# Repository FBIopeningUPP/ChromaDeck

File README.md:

# ChromaDeck

this project is basically a midi deivce that is good and i lov eit

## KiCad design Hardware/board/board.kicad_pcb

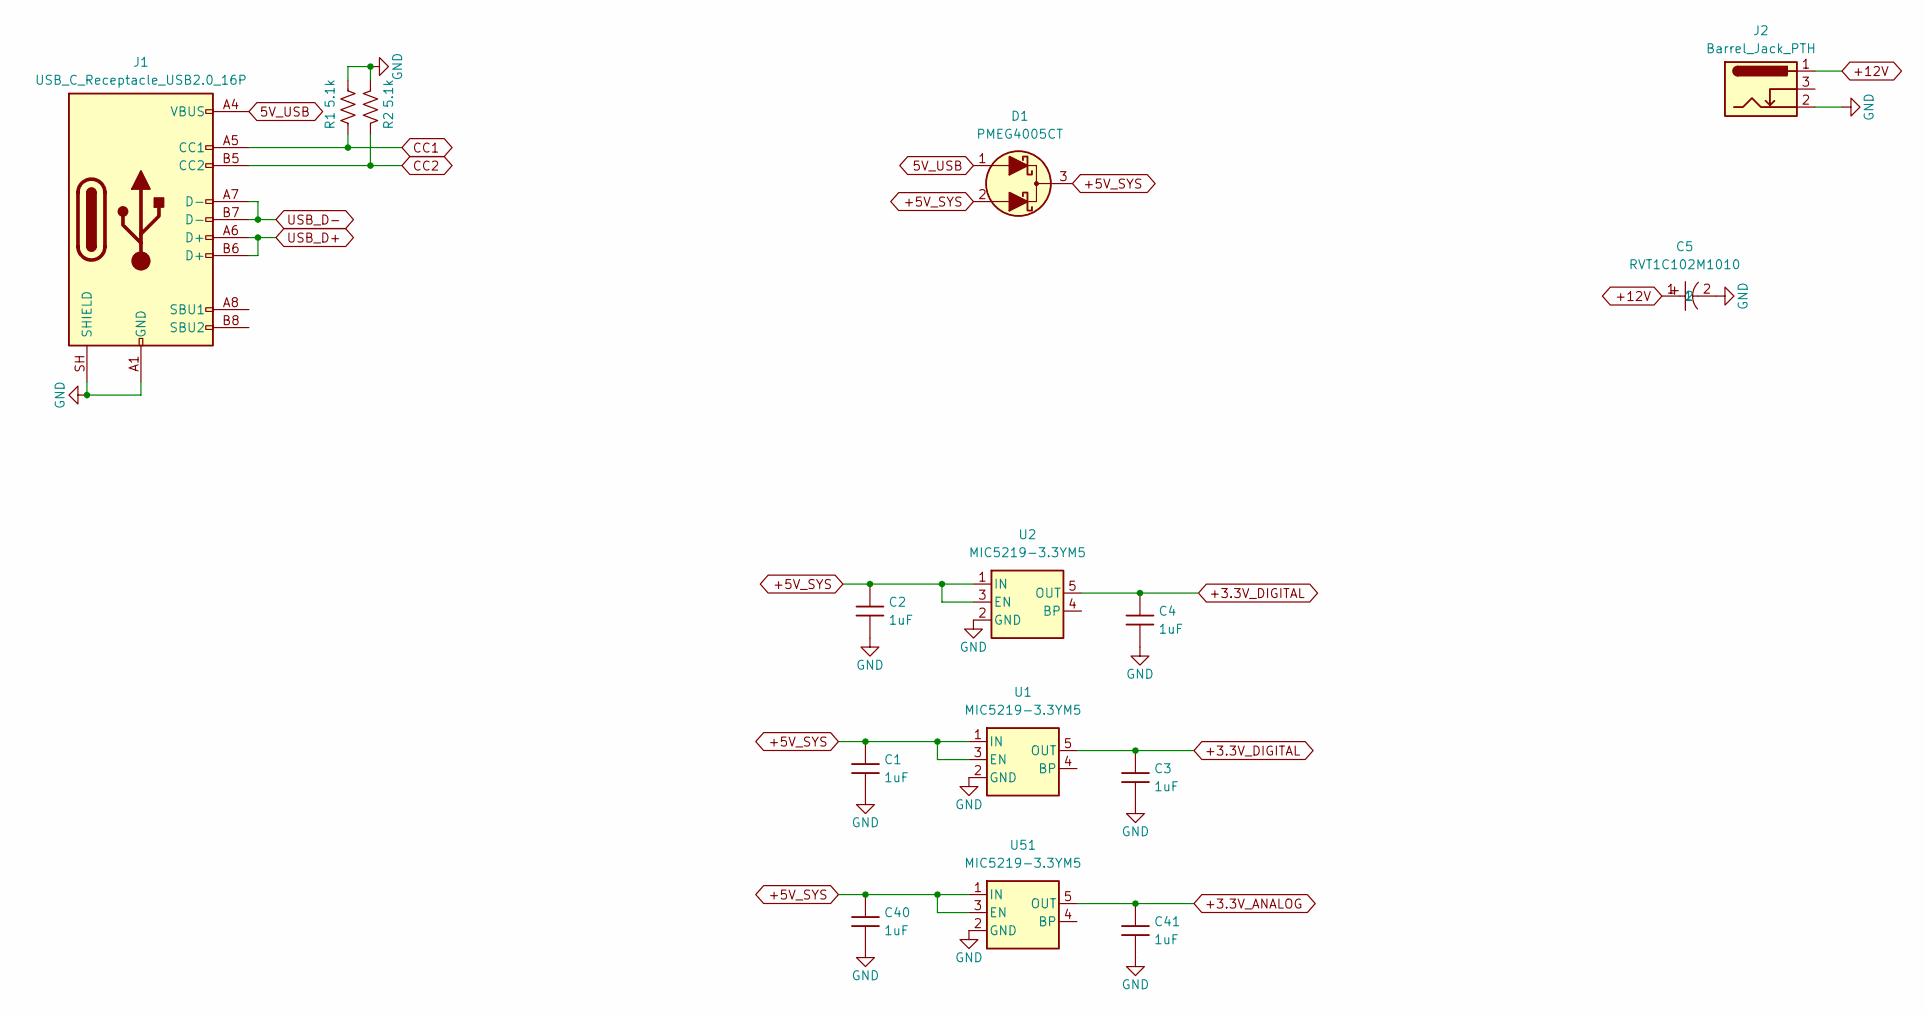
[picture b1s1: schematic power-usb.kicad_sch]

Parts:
C1, C2, C3, C4, C40, C41: 1uF; C_0603
C5: RVT1C102M1010; CAP-SMD_BD10.0-L10.3-W10.3-LS11.3-FD; MPN RVT1C102M1010; LCSC Part C72470
D1: PMEG4005CT; SOT-23
J1: USB_C_Receptacle_USB2.0_16P; USB_C_Receptacle_GCT_USB4105-xx-A_16P_TopMnt_Horizontal
J2: Barrel_Jack_PTH; BarrelJack_CUI_PJ-102AH_Horizontal
R1, R2: 5.1k; R_0603_1608Metric
U1, U2, U51: MIC5219-3.3YM5; SOT-23-5

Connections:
5V_USB: D1.1 (A2), J1.A4 (VBUS), J1.A9 (VBUS), J1.B4 (VBUS), J1.B9 (VBUS)
+3.3V_ANALOG: C41.1, U51.5 (OUT); also elsewhere on the board
+3.3V_DIGITAL: C3.1, C4.1, U1.5 (OUT), U2.5 (OUT); also elsewhere on the board
+5V_SYS: C1.1, C2.1, C40.1, D1.2 (A1), D1.3 (K), U1.1 (IN), U1.3 (EN), U2.1 (IN), U2.3 (EN), U51.1 (IN), U51.3 (EN); also elsewhere on the board
+12V: C5.1, J2.1 (PWR); also elsewhere on the board
CC1: J1.A5 (CC1), R1.2
CC2: J1.B5 (CC2), R2.2
GND: C1.2, C2.2, C3.2, C4.2, C5.2, C40.2, C41.2, J1.A1 (GND), J1.A12 (GND), J1.B1 (GND), J1.B12 (GND), J1.SH (SHIELD), J2.2 (GND), R1.1, R2.1, U1.2 (GND), U2.2 (GND), U51.2 (GND); also elsewhere on the board
USB_D+: J1.A6 (D+), J1.B6 (D+); also elsewhere on the board
USB_D-: J1.A7 (D-), J1.B7 (D-); also elsewhere on the board

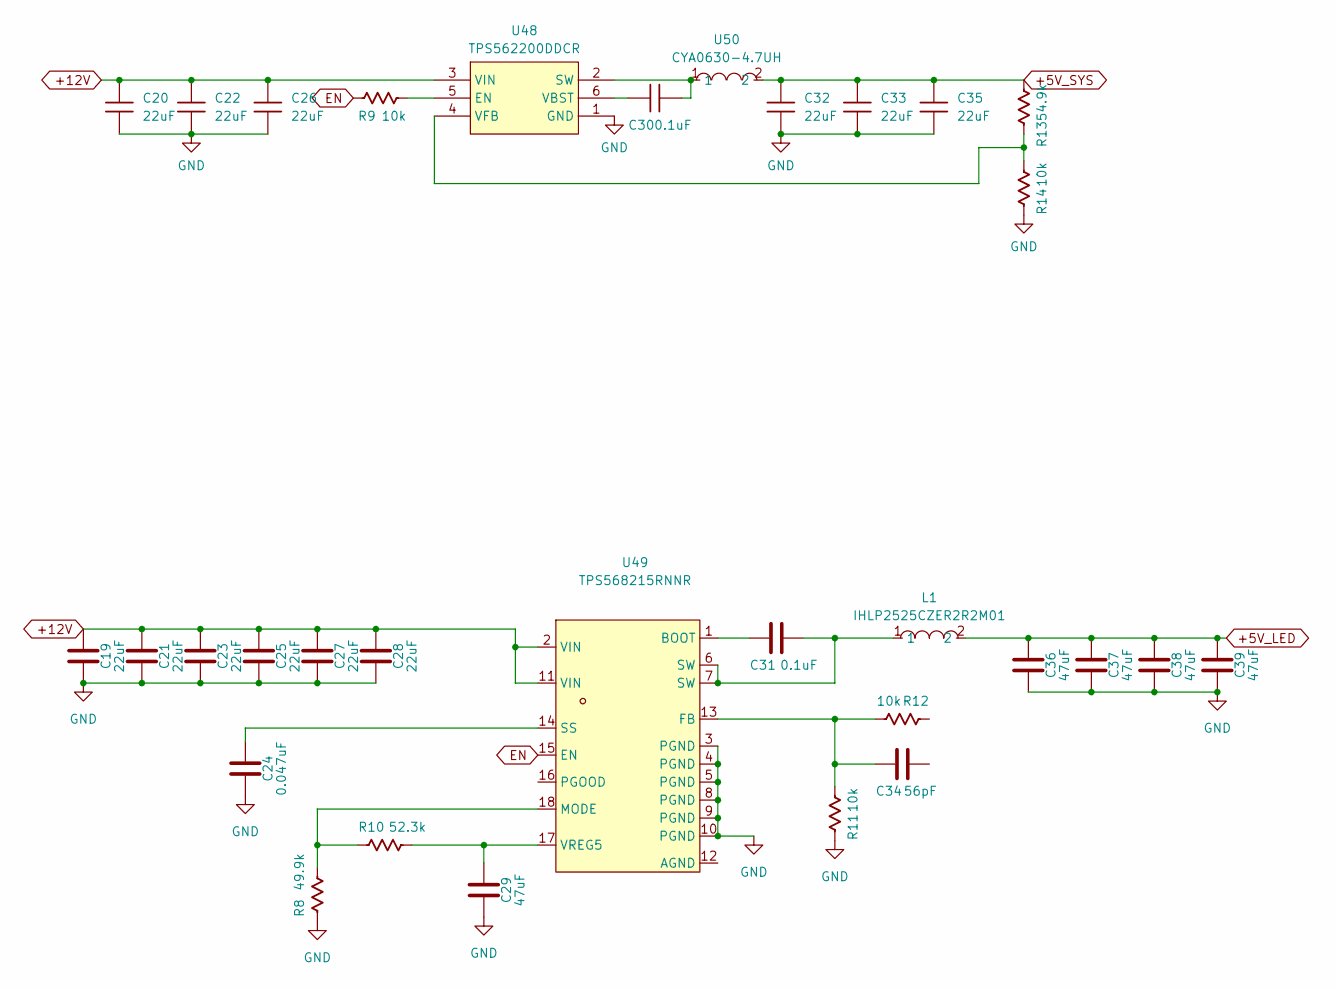
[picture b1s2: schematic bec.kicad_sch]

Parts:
C19, C21, C23, C25, C27, C28: 22uF; C_0805_2012Metric
C20, C22, C26, C32, C33, C35: 22uF; C_0603
C24: 0.047uF; C_0603_1608Metric
C29, C36, C37, C38, C39: 47uF; C_0805_2012Metric
C30: 0.1uF; C_0603
C31: 0.1uF; C_0805_2012Metric
C34: 56pF; C_0805_2012Metric
L1: IHLP2525CZER2R2M01; IND-SMD_L6.5-W6.5_IHLP-2525; MPN IHLP2525CZER2R2M01; LCSC Part C540967
R8: 49.9k; R_0603_1608Metric
R9, R11, R12, R14: 10k; R_0603_1608Metric
R10: 52.3k; R_0603_1608Metric
R13: 54.9k; R_0603_1608Metric
U48: TPS562200DDCR; SOT-23-6_L2.9-W1.6-P0.95-LS2.8-BR; MPN TPS562200DDCR; LCSC Part C49757
U49: TPS568215RNNR; VQFN-HR-18_L3.5-W3.5-P0.55-BL_TPS56C215RNNR; MPN TPS568215RNNR; LCSC Part C473367
U50: CYA0630-4.7UH; IND-SMD_L7.2-W6.6_GPSR07X0; MPN CYA0630-4.7UH; LCSC Part C5189748

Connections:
+5V_LED: C36.2, C37.2, C38.2, C39.2, L1.2; also elsewhere on the board
+5V_SYS: C32.1, C33.1, C35.1, R13.2, U50.2; also elsewhere on the board
+12V: C19.2, C20.1, C21.2, C22.1, C23.2, C25.2, C26.1, C27.2, C28.2, U48.3 (VIN), U49.2 (VIN), U49.11 (VIN); also elsewhere on the board
EN: R9.1, U49.15 (EN)
GND: C19.1, C20.2, C21.1, C22.2, C23.1, C24.1, C25.1, C26.2, C27.1, C28.1, C29.1, C32.2, C33.2, C35.2, C36.1, C37.1, C38.1, C39.1, R8.2, R11.1, R14.1, U48.1 (GND), U49.3 (PGND), U49.4 (PGND), U49.5 (PGND), U49.8 (PGND), U49.9 (PGND), U49.10 (PGND); also elsewhere on the board
unnamed: C31.2, L1.1, U49.6 (SW), U49.7 (SW)
unnamed: R9.2, U48.5 (EN)
unnamed: C30.2, U48.2 (SW), U50.1
unnamed: C30.1, U48.6 (VBST)
unnamed: R13.1, R14.2, U48.4 (VFB)
unnamed: C31.1, U49.1 (BOOT)
unnamed: C34.1, R11.2, R12.2, U49.13 (FB)
unnamed: R8.1, R10.2, U49.18 (MODE)
unnamed: C24.2, U49.14 (SS)
unnamed: C29.2, R10.1, U49.17 (VREG5)

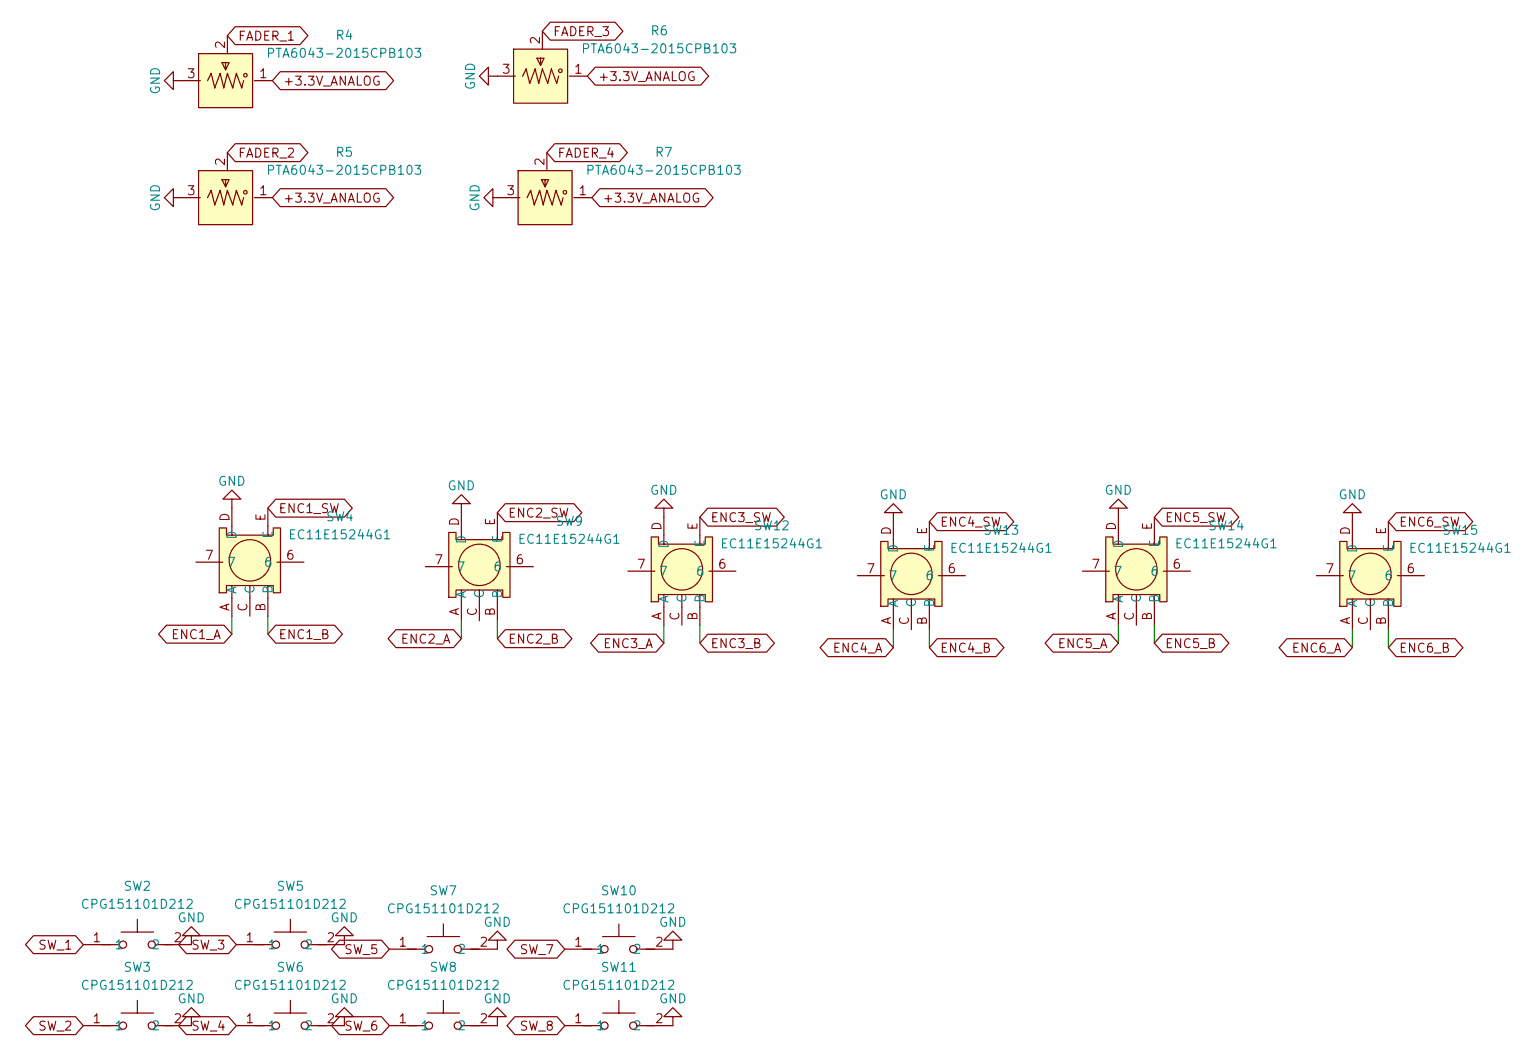
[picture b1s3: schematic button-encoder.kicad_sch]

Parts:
R4, R5, R6, R7: PTA6043-2015CPB103; RES-ADJ-TH_PTA6043-2015DPB103; MPN PTA6043-2015CPB103; LCSC Part C17203852
SW2, SW3, SW5, SW6, SW7, SW8, SW10, SW11: CPG151101D212; KEY-TH_CPG151101D21X; MPN CPG151101D212; LCSC Part C400234
SW4, SW9, SW12, SW13, SW14, SW15: EC11E15244G1; SW-TH_EC11E15244G1; MPN EC11E15244G1; LCSC Part C370970

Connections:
+3.3V_ANALOG: R4.1, R5.1, R6.1, R7.1; also elsewhere on the board
ENC1_A: SW4.A; also elsewhere on the board
ENC1_B: SW4.B; also elsewhere on the board
ENC1_SW: SW4.E; also elsewhere on the board
ENC2_A: SW9.A; also elsewhere on the board
ENC2_B: SW9.B; also elsewhere on the board
ENC2_SW: SW9.E; also elsewhere on the board
ENC3_A: SW12.A; also elsewhere on the board
ENC3_B: SW12.B; also elsewhere on the board
ENC3_SW: SW12.E; also elsewhere on the board
ENC4_A: SW13.A; also elsewhere on the board
ENC4_B: SW13.B; also elsewhere on the board
ENC4_SW: SW13.E; also elsewhere on the board
ENC5_A: SW14.A; also elsewhere on the board
ENC5_B: SW14.B; also elsewhere on the board
ENC5_SW: SW14.E; also elsewhere on the board
ENC6_A: SW15.A; also elsewhere on the board
ENC6_B: SW15.B; also elsewhere on the board
ENC6_SW: SW15.E; also elsewhere on the board
FADER_1: R4.2
FADER_2: R5.2
FADER_3: R6.2
FADER_4: R7.2
GND: R4.3, R5.3, R6.3, R7.3, SW2.2, SW3.2, SW4.D, SW5.2, SW6.2, SW7.2, SW8.2, SW9.D, SW10.2, SW11.2, SW12.D, SW13.D, SW14.D, SW15.D; also elsewhere on the board
SW_1: SW2.1; also elsewhere on the board
SW_2: SW3.1; also elsewhere on the board
SW_3: SW5.1; also elsewhere on the board
SW_4: SW6.1; also elsewhere on the board
SW_5: SW7.1; also elsewhere on the board
SW_6: SW8.1; also elsewhere on the board
SW_7: SW10.1; also elsewhere on the board
SW_8: SW11.1; also elsewhere on the board

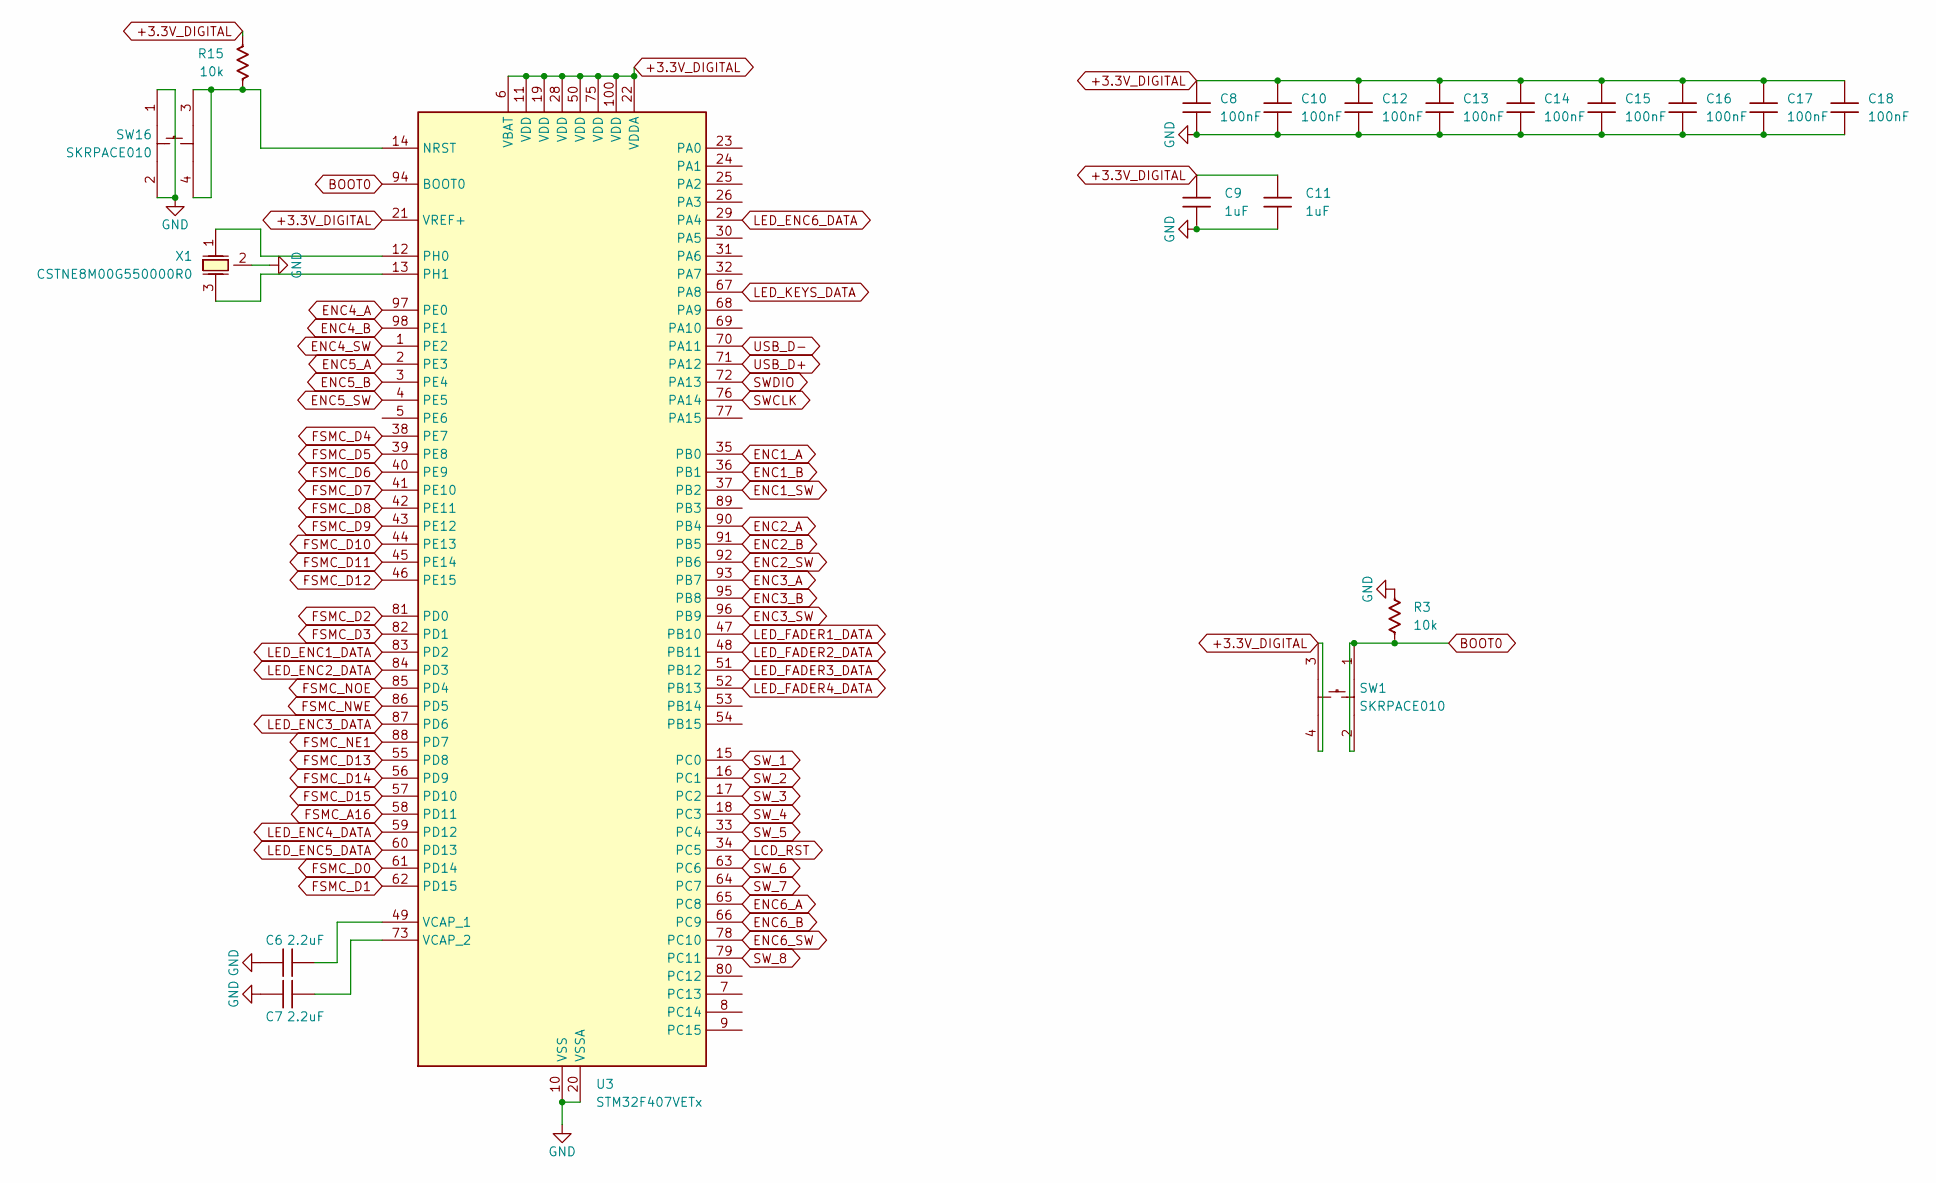
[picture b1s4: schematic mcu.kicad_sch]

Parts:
C6, C7: 2.2uF; C_0603
C8, C10, C12, C13, C14, C15, C16, C17, C18: 100nF; C_0603
C9, C11: 1uF; C_0603
R3, R15: 10k; R_0603_1608Metric
SW1, SW16: SKRPACE010; KEY-SMD_4P-L4.2-W3.2-P2.20-LS4.6; MPN SKRPACE010; LCSC Part C139797
U3: STM32F407VETx; LQFP-100_14x14mm_P0.5mm
X1: CSTNE8M00G550000R0; OSC-SMD_3P-L3.2-W1.3-P1.20-L; MPN CSTNE8M00G550000R0; LCSC Part C341522

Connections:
+3.3V_DIGITAL: C8.1, C9.1, C10.1, C11.1, C12.1, C13.1, C14.1, C15.1, C16.1, C17.1, C18.1, R15.2, SW1.3, SW1.4, U3.6 (VBAT), U3.11 (VDD), U3.19 (VDD), U3.21 (VREF+), U3.22 (VDDA), U3.28 (VDD), U3.50 (VDD), U3.75 (VDD), U3.100 (VDD); also elsewhere on the board
BOOT0: R3.1, SW1.1, SW1.2, U3.94 (BOOT0)
ENC1_A: U3.35 (PB0); also elsewhere on the board
ENC1_B: U3.36 (PB1); also elsewhere on the board
ENC1_SW: U3.37 (PB2); also elsewhere on the board
ENC2_A: U3.90 (PB4); also elsewhere on the board
ENC2_B: U3.91 (PB5); also elsewhere on the board
ENC2_SW: U3.92 (PB6); also elsewhere on the board
ENC3_A: U3.93 (PB7); also elsewhere on the board
ENC3_B: U3.95 (PB8); also elsewhere on the board
ENC3_SW: U3.96 (PB9); also elsewhere on the board
ENC4_A: U3.97 (PE0); also elsewhere on the board
ENC4_B: U3.98 (PE1); also elsewhere on the board
ENC4_SW: U3.1 (PE2); also elsewhere on the board
ENC5_A: U3.2 (PE3); also elsewhere on the board
ENC5_B: U3.3 (PE4); also elsewhere on the board
ENC5_SW: U3.4 (PE5); also elsewhere on the board
ENC6_A: U3.65 (PC8); also elsewhere on the board
ENC6_B: U3.66 (PC9); also elsewhere on the board
ENC6_SW: U3.78 (PC10); also elsewhere on the board
FSMC_A16: U3.58 (PD11); also elsewhere on the board
FSMC_D0: U3.61 (PD14); also elsewhere on the board
FSMC_D1: U3.62 (PD15); also elsewhere on the board
FSMC_D2: U3.81 (PD0); also elsewhere on the board
FSMC_D3: U3.82 (PD1); also elsewhere on the board
FSMC_D4: U3.38 (PE7); also elsewhere on the board
FSMC_D5: U3.39 (PE8); also elsewhere on the board
FSMC_D6: U3.40 (PE9); also elsewhere on the board
FSMC_D7: U3.41 (PE10); also elsewhere on the board
FSMC_D8: U3.42 (PE11); also elsewhere on the board
FSMC_D9: U3.43 (PE12); also elsewhere on the board
FSMC_D10: U3.44 (PE13); also elsewhere on the board
FSMC_D11: U3.45 (PE14); also elsewhere on the board
FSMC_D12: U3.46 (PE15)
FSMC_D13: U3.55 (PD8); also elsewhere on the board
FSMC_D14: U3.56 (PD9); also elsewhere on the board
FSMC_D15: U3.57 (PD10); also elsewhere on the board
FSMC_NE1: U3.88 (PD7); also elsewhere on the board
FSMC_NOE: U3.85 (PD4); also elsewhere on the board
FSMC_NWE: U3.86 (PD5); also elsewhere on the board
GND: C6.1, C7.1, C8.2, C9.2, C10.2, C11.2, C12.2, C13.2, C14.2, C15.2, C16.2, C17.2, C18.2, R3.2, SW16.1, SW16.2, U3.10 (VSS), U3.20 (VSSA), U3.27 (VSS), U3.74 (VSS), U3.99 (VSS), X1.2; also elsewhere on the board
LCD_RST: U3.34 (PC5); also elsewhere on the board
LED_ENC1_DATA: U3.83 (PD2); also elsewhere on the board
LED_ENC2_DATA: U3.84 (PD3); also elsewhere on the board
LED_ENC3_DATA: U3.87 (PD6); also elsewhere on the board
LED_ENC4_DATA: U3.59 (PD12); also elsewhere on the board
LED_ENC5_DATA: U3.60 (PD13); also elsewhere on the board
LED_ENC6_DATA: U3.29 (PA4)
LED_FADER1_DATA: U3.47 (PB10); also elsewhere on the board
LED_FADER2_DATA: U3.48 (PB11); also elsewhere on the board
LED_FADER3_DATA: U3.51 (PB12); also elsewhere on the board
LED_FADER4_DATA: U3.52 (PB13); also elsewhere on the board
LED_KEYS_DATA: U3.67 (PA8); also elsewhere on the board
unnamed: R15.1, SW16.3, SW16.4, U3.14 (NRST)
unnamed: U3.12 (PH0), X1.1
unnamed: U3.13 (PH1), X1.3
unnamed: C6.2, U3.49 (VCAP_1)
unnamed: C7.2, U3.73 (VCAP_2)
SWCLK: U3.76 (PA14)
SWDIO: U3.72 (PA13)
SW_1: U3.15 (PC0); also elsewhere on the board
SW_2: U3.16 (PC1); also elsewhere on the board
SW_3: U3.17 (PC2); also elsewhere on the board
SW_4: U3.18 (PC3); also elsewhere on the board
SW_5: U3.33 (PC4); also elsewhere on the board
SW_6: U3.63 (PC6); also elsewhere on the board
SW_7: U3.64 (PC7); also elsewhere on the board
SW_8: U3.79 (PC11); also elsewhere on the board
USB_D+: U3.71 (PA12); also elsewhere on the board
USB_D-: U3.70 (PA11); also elsewhere on the board

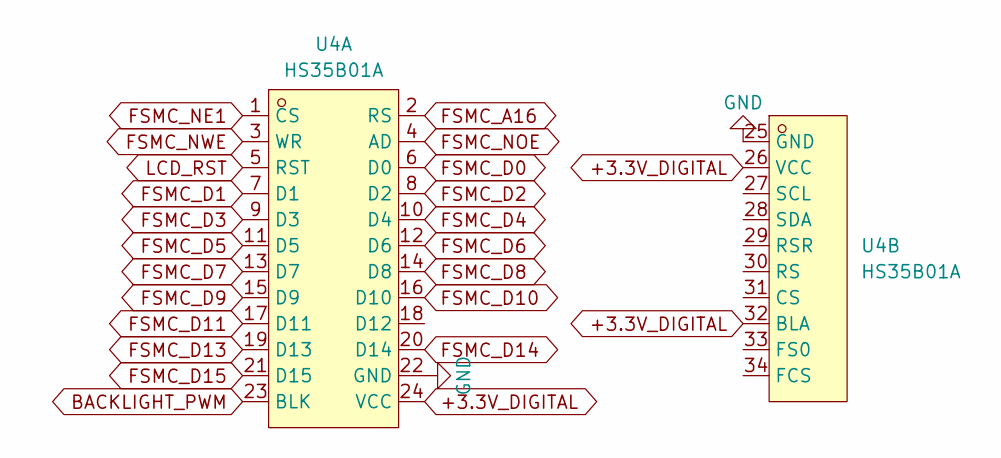
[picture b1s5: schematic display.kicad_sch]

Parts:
U4: HS35B01A; LCD-TH_L96.5-W57.3_HS35B01A; MPN HS35B01A; LCSC Part C19632787

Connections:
+3.3V_DIGITAL: U4.24 (VCC), U4.26 (VCC), U4.32 (BLA); also elsewhere on the board
BACKLIGHT_PWM: U4.23 (BLK)
FSMC_A16: U4.2 (RS); also elsewhere on the board
FSMC_D0: U4.6 (D0); also elsewhere on the board
FSMC_D1: U4.7 (D1); also elsewhere on the board
FSMC_D2: U4.8 (D2); also elsewhere on the board
FSMC_D3: U4.9 (D3); also elsewhere on the board
FSMC_D4: U4.10 (D4); also elsewhere on the board
FSMC_D5: U4.11 (D5); also elsewhere on the board
FSMC_D6: U4.12 (D6); also elsewhere on the board
FSMC_D7: U4.13 (D7); also elsewhere on the board
FSMC_D8: U4.14 (D8); also elsewhere on the board
FSMC_D9: U4.15 (D9); also elsewhere on the board
FSMC_D10: U4.16 (D10); also elsewhere on the board
FSMC_D11: U4.17 (D11); also elsewhere on the board
FSMC_D13: U4.19 (D13); also elsewhere on the board
FSMC_D14: U4.20 (D14); also elsewhere on the board
FSMC_D15: U4.21 (D15); also elsewhere on the board
FSMC_NE1: U4.1 (CS); also elsewhere on the board
FSMC_NOE: U4.4 (AD); also elsewhere on the board
FSMC_NWE: U4.3 (WR); also elsewhere on the board
GND: U4.22 (GND), U4.25 (GND); also elsewhere on the board
LCD_RST: U4.5 (RST); also elsewhere on the board

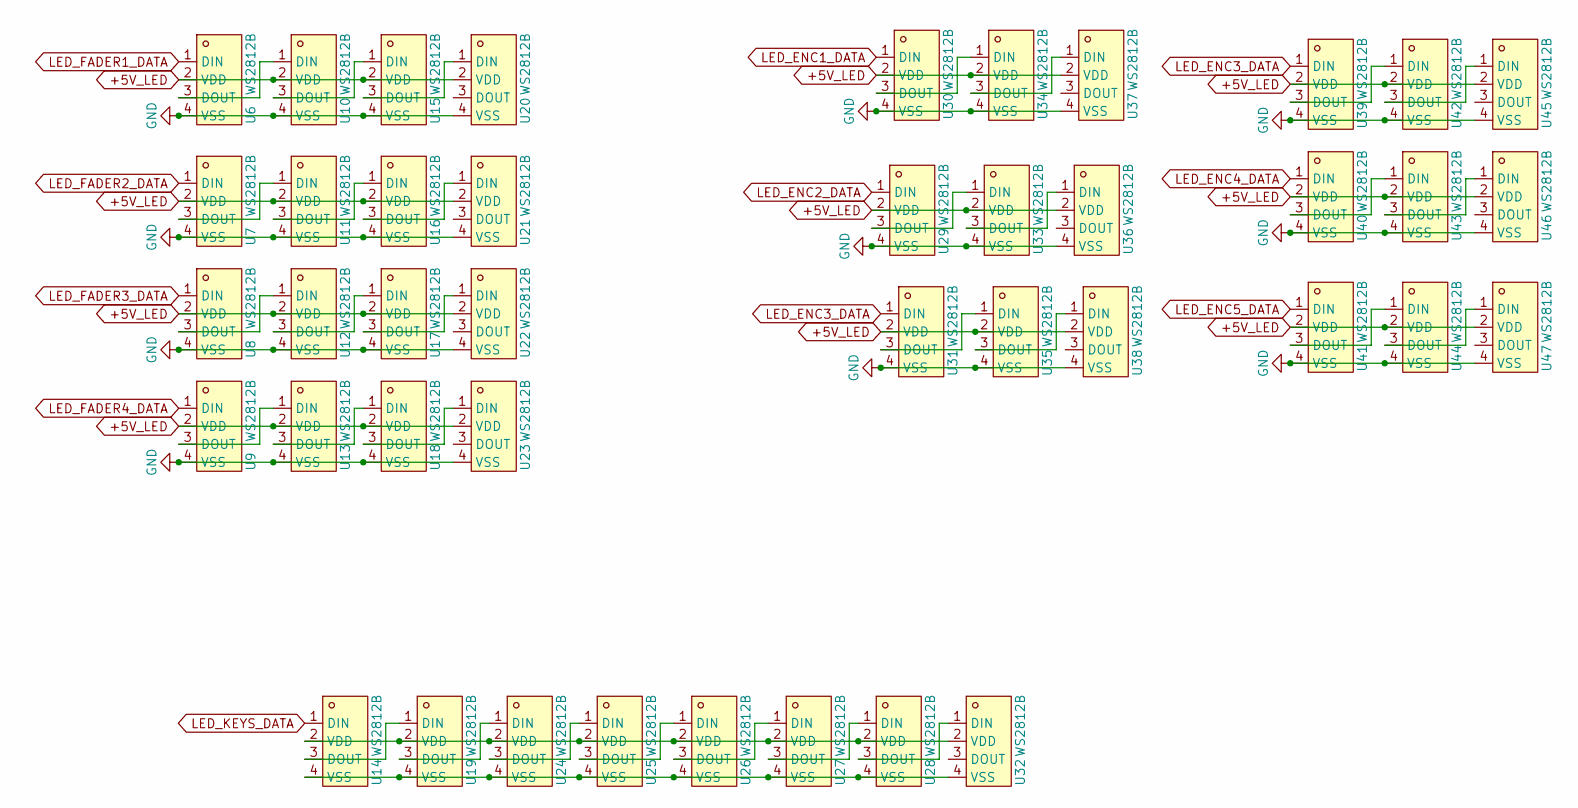
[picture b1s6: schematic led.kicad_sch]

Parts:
U6, U7, U8, U9, U10, U11, U12, U13, U14, U15, U16, U17, U18, U19, U20, U21, U22, U23, U24, U25, U26, U27, U28, U29, U30, U31, U32, U33, U34, U35, U36, U37, U38, U39, U40, U41, U42, U43, U44, U45, U46, U47: WS2812B; LED-SMD_4P-L4.0-W1.7-R; MPN WS2812B-4020-G1; LCSC Part C42417614

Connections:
+5V_LED: U6.2 (VDD), U7.2 (VDD), U8.2 (VDD), U9.2 (VDD), U10.2 (VDD), U11.2 (VDD), U12.2 (VDD), U13.2 (VDD), U15.2 (VDD), U16.2 (VDD), U17.2 (VDD), U18.2 (VDD), U20.2 (VDD), U21.2 (VDD), U22.2 (VDD), U23.2 (VDD), U29.2 (VDD), U30.2 (VDD), U31.2 (VDD), U33.2 (VDD), U34.2 (VDD), U35.2 (VDD), U36.2 (VDD), U37.2 (VDD), U38.2 (VDD), U39.2 (VDD), U40.2 (VDD), U41.2 (VDD), U42.2 (VDD), U43.2 (VDD), U44.2 (VDD), U45.2 (VDD), U46.2 (VDD), U47.2 (VDD); also elsewhere on the board
GND: U6.4 (VSS), U7.4 (VSS), U8.4 (VSS), U9.4 (VSS), U10.4 (VSS), U11.4 (VSS), U12.4 (VSS), U13.4 (VSS), U15.4 (VSS), U16.4 (VSS), U17.4 (VSS), U18.4 (VSS), U20.4 (VSS), U21.4 (VSS), U22.4 (VSS), U23.4 (VSS), U29.4 (VSS), U30.4 (VSS), U31.4 (VSS), U33.4 (VSS), U34.4 (VSS), U35.4 (VSS), U36.4 (VSS), U37.4 (VSS), U38.4 (VSS), U39.4 (VSS), U40.4 (VSS), U41.4 (VSS), U42.4 (VSS), U43.4 (VSS), U44.4 (VSS), U45.4 (VSS), U46.4 (VSS), U47.4 (VSS); also elsewhere on the board
LED_ENC1_DATA: U30.1 (DIN); also elsewhere on the board
LED_ENC2_DATA: U29.1 (DIN); also elsewhere on the board
LED_ENC3_DATA: U31.1 (DIN), U39.1 (DIN); also elsewhere on the board
LED_ENC4_DATA: U40.1 (DIN); also elsewhere on the board
LED_ENC5_DATA: U41.1 (DIN); also elsewhere on the board
LED_FADER1_DATA: U6.1 (DIN); also elsewhere on the board
LED_FADER2_DATA: U7.1 (DIN); also elsewhere on the board
LED_FADER3_DATA: U8.1 (DIN); also elsewhere on the board
LED_FADER4_DATA: U9.1 (DIN); also elsewhere on the board
LED_KEYS_DATA: U14.1 (DIN); also elsewhere on the board
unnamed: U6.3 (DOUT), U10.1 (DIN)
unnamed: U10.3 (DOUT), U15.1 (DIN)
unnamed: U7.3 (DOUT), U11.1 (DIN)
unnamed: U11.3 (DOUT), U16.1 (DIN)
unnamed: U8.3 (DOUT), U12.1 (DIN)
unnamed: U12.3 (DOUT), U17.1 (DIN)
unnamed: U9.3 (DOUT), U13.1 (DIN)
unnamed: U13.3 (DOUT), U18.1 (DIN)
unnamed: U14.3 (DOUT), U19.1 (DIN)
unnamed: U14.2 (VDD), U19.2 (VDD), U24.2 (VDD), U25.2 (VDD), U26.2 (VDD), U27.2 (VDD), U28.2 (VDD), U32.2 (VDD)
unnamed: U14.4 (VSS), U19.4 (VSS), U24.4 (VSS), U25.4 (VSS), U26.4 (VSS), U27.4 (VSS), U28.4 (VSS), U32.4 (VSS)
unnamed: U15.3 (DOUT), U20.1 (DIN)
unnamed: U16.3 (DOUT), U21.1 (DIN)
unnamed: U17.3 (DOUT), U22.1 (DIN)
unnamed: U18.3 (DOUT), U23.1 (DIN)
unnamed: U19.3 (DOUT), U24.1 (DIN)
unnamed: U24.3 (DOUT), U25.1 (DIN)
unnamed: U25.3 (DOUT), U26.1 (DIN)
unnamed: U26.3 (DOUT), U27.1 (DIN)
unnamed: U27.3 (DOUT), U28.1 (DIN)
unnamed: U28.3 (DOUT), U32.1 (DIN)
unnamed: U29.3 (DOUT), U33.1 (DIN)
unnamed: U30.3 (DOUT), U34.1 (DIN)
unnamed: U31.3 (DOUT), U35.1 (DIN)
unnamed: U33.3 (DOUT), U36.1 (DIN)
unnamed: U34.3 (DOUT), U37.1 (DIN)
unnamed: U35.3 (DOUT), U38.1 (DIN)
unnamed: U39.3 (DOUT), U42.1 (DIN)
unnamed: U40.3 (DOUT), U43.1 (DIN)
unnamed: U41.3 (DOUT), U44.1 (DIN)
unnamed: U42.3 (DOUT), U45.1 (DIN)
unnamed: U43.3 (DOUT), U46.1 (DIN)
unnamed: U44.3 (DOUT), U47.1 (DIN)

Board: 2 copper layers, 127 parts (0 on the bottom side), 117 nets, no tracks yet.

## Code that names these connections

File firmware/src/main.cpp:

#include <Arduino.h>
#include <Adafruit_TinyUSB.h>
#include <MIDI.h>

#include "ChromaKey.h"
#include "ChromaFader.h"
#include "ChromaEncoder.h"
#include "LEDManager.h"
#include "DisplayManager.h"

Adafruit_USBD_MIDI usb_midi;
MIDI_CREATE_INSTANCE(Adafruit_USBD_MIDI, usb_midi, MIDI);

ChromaKey keys[8] = {
    ChromaKey(PC0, 36), ChromaKey(PC1, 37), ChromaKey(PC2, 38), ChromaKey(PC3, 39),
    ChromaKey(PC4, 40), ChromaKey(PC6, 41), ChromaKey(PC7, 42), ChromaKey(PC11, 43)
};

ChromaFader faders[4] = {
    ChromaFader(PA0, 1), ChromaFader(PA1, 2), ChromaFader(PA2, 3), ChromaFader(PA3, 4)
};

ChromaEncoder encoders[6] = {
    ChromaEncoder(PB0, PB1, PB2, 5),
    ChromaEncoder(PB4, PB5, PB6, 6),
    ChromaEncoder(PB7, PB8, PB9, 7),
    ChromaEncoder(PE0, PE1, PE2, 8),
    ChromaEncoder(PE3, PE4, PE5, 9),
    ChromaEncoder(PC8, PC9, PC10, 10)
};

LEDManager leds;
DisplayManager display;

int currentFaderValues[4] = {0};
int currentEncoderValues[6] = {0};
unsigned long lastDisplayUpdate = 0;

void setup() {
    usb_midi.begin();
    MIDI.begin(MIDI_CHANNEL_OMNI);

    for (int i = 0; i < 8; i++) keys[i].begin();
    for (int i = 0; i < 4; i++) faders[i].begin();
    for (int i = 0; i < 6; i++) encoders[i].begin();

    leds.begin();
    display.begin();
}

void loop() {
    bool graphicsNeedUpdate = false;

    for (int i = 0; i < 8; i++) {
        if (keys[i].update()) {
            MIDI.sendNoteOn(keys[i].getNote(), 127, 1);
            leds.setKeyColor(i, CRGB::Red);
        } else if (!keys[i].getState()) {
            leds.setKeyColor(i, CRGB::Black);
        }
    }

    for (int i = 0; i < 4; i++) {
        if (faders[i].update()) {
            currentFaderValues[i] = faders[i].getValue();
            MIDI.sendControlChange(faders[i].getCC(), currentFaderValues[i], 1);
            leds.setFaderLevel(i, currentFaderValues[i], CRGB::Cyan);
            graphicsNeedUpdate = true;
        }
    }

    for (int i = 0; i < 6; i++) {
        if (encoders[i].updateTurn()) {
            currentEncoderValues[i] = encoders[i].getValue();
            MIDI.sendControlChange(encoders[i].getCC(), currentEncoderValues[i], 1);
            leds.setEncoderRing(i, currentEncoderValues[i], CRGB::Magenta);
            graphicsNeedUpdate = true;
        }
        if (encoders[i].updateSwitch()) {
            MIDI.sendNoteOn(50 + i, 127, 1);
        }
    }

    leds.update();

    if (graphicsNeedUpdate || (millis() - lastDisplayUpdate > 33)) {
        display.drawDashboard(currentFaderValues, currentEncoderValues);
        lastDisplayUpdate = millis();
    }
}

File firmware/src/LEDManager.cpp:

#include "LEDManager.h"

LEDManager::LEDManager() {}

void LEDManager::begin() {
    FastLED.addLeds<WS2812B, PA8, GRB>(keysLeds, 8);

    FastLED.addLeds<WS2812B, PB10, GRB>(faderLeds[0], 10);
    FastLED.addLeds<WS2812B, PB11, GRB>(faderLeds[1], 10);
    FastLED.addLeds<WS2812B, PB12, GRB>(faderLeds[2], 10);
    FastLED.addLeds<WS2812B, PB13, GRB>(faderLeds[3], 10);

    FastLED.addLeds<WS2812B, PD2, GRB>(encoderLeds[0], 12);
    FastLED.addLeds<WS2812B, PD3, GRB>(encoderLeds[1], 12);
    FastLED.addLeds<WS2812B, PD6, GRB>(encoderLeds[2], 12);
    FastLED.addLeds<WS2812B, PD12, GRB>(encoderLeds[3], 12);
    FastLED.addLeds<WS2812B, PD13, GRB>(encoderLeds[4], 12);
    FastLED.addLeds<WS2812B, PA4, GRB>(encoderLeds[5], 12);

    FastLED.setBrightness(100);
}

void LEDManager::update() {
    FastLED.show();
}

void LEDManager::setKeyColor(uint8_t index, CRGB color) {
    if (index < 8) {
        keysLeds[index] = color;
    }
}

void LEDManager::setFaderLevel(uint8_t index, uint8_t level, CRGB color) {
    if (index < 4) {
        uint8_t numLedsToLight = map(level, 0, 127, 0, 10);
        for (uint8_t i = 0; i < 10; i++) {
            if (i < numLedsToLight) {
                faderLeds[index][i] = color;
            } else {
                faderLeds[index][i] = CRGB::Black;
            }
        }
    }
}

void LEDManager::setEncoderRing(uint8_t index, uint8_t level, CRGB color) {
    if (index < 6) {
        uint8_t numLedsToLight = map(level, 0, 127, 0, 12);
        for (uint8_t i = 0; i < 12; i++) {
            if (i < numLedsToLight) {
                encoderLeds[index][i] = color;
            } else {
                encoderLeds[index][i] = CRGB::Black;
            }
        }
    }
}
